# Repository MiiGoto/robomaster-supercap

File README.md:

# Firmware implementation — 2026-10-08

Current: Rev A STM32G474RET6 firmware source implemented; default SAFE_MONITOR_ONLY. Host logic tests and ARM builds are recorded in [docs/firmware_validation.md](docs/firmware_validation.md). No flash, option-byte write, real PWM/contact actuation or energizing was performed. Hardware/CAD is unchanged. Calibration, control gains, timing, BQ physical behavior and power limits require bench measurement and human review before first flash/energizing.

Current guides: [firmware architecture](docs/firmware_architecture.md), [operation](docs/supercap_user_guide.md), [commissioning](docs/firmware_commissioning.md), [CAN protocol](docs/can_protocol.md), [tuning](docs/control_tuning.md), [flash setup](docs/firmware_flash_setup.md).

## Historical records (preserved)

# PCB routing complete — 2026-10-07

**Current: Prototype Rev A CAD routing complete.** KiCad10.0.6の正式PCBでnative未接続0、全DRC0 errors/0 warnings、schematic parity0、ERC0 errors/0 warningsを確認した。全331ネット／1524 net-assigned pad recordsの物理接続と、設計manifestの1478 pad/net assignmentsを照合済み。これはCAD接続・規則検証であり、製造リリース、通電許可、120 W性能、競技適合の承認ではない。

一般銅箔間隔0.20 mm、承認済み39 ICの同一部品内Pad/Pad0.15 mmを維持した。新たなDRC除外・No ERC・規則緩和はない。未コミットの`.kicad_pro`設定展開は保持し、functional commitに含めない。詳細は[配線完了記録](docs/pcb_routing_completion.md)を現在の情報源とする。以下は過去時点の記録として保存する。

## Historical records (preserved)

# Routing checkpoint — 2026-10-04

**Routing incomplete.** 保存したPCBは電力7ネットの全パッド接続と、局所GND/一部信号配線を追加したcheckpoint。native未接続 **610本**（239 nets）、寸法・間隔DRC **0 errors/0 warnings**、schematic parity0。元の935本から325本を解消したが、配線完成/製造/通電/性能保証は意味しない。

現在の結果と残りを[配線作業記録](docs/pcb_routing_completion.md)で確認する。以下は以前の経緯を含む。

# Clearance approval update — 2026-10-04

39対象ICの内部fine-pitchパッド間0.15 mmをユーザー承認に基づき許容し、その他の銅箔間隔は0.20 mm以上を維持した。DRCの寸法・間隔違反0/0、未接続935本。[検証記録](docs/pcb_rev_a_validation.md)を現状として優先する。以下は変更前の経緯を含む。

# PCB engineering authorized — 2026-10-04

ユーザーがsurge・OC遮断時間・fuse/接触器協調・熱・放電時間の実測前にPCB配置/配線へ進むことを明示承認した。[現行PCB記録](docs/pcb_rev_a.md)を優先する。未実測の項目はPrototype Assumptionとして保持し、製造/通電/性能保証にはしない。以下の「PCB未承認/開始しない」は過去時点の記録として残す。

## Historical records (preserved)

# Prototype Rev A — 2026-10-04 delegated decisions

ユーザーの委任に基づき、セル監視RAM設定・exact passive選定・外部ベンチ遮断アセンブリ・保護/熱/放電検証基準を[現行選定書](docs/rev_a_design_freeze.md)へ確定した。選定はPrototype Assumption、実測検証は未実施。平均cap電流の初期上限9.5 A、OC約12 A、目標遮断0.5 µs、各link bulk6×470 µF、precharge timeout3 s。12 A/120 Wは後続の検証目標として保持。PCB placement/通電は開始しない。以下の2026-10-03以前の未選定表示は経緯記録であり、この選定書が優先する。

# Prototype Rev A — current status

2026-10-03 JST。**Current: Prototype Rev A schematic only.** Task2 architectureはユーザー採用承認済み。実機条件未確認は[Prototype envelope](docs/prototype_rev_a_envelope.md)に明示した **ASSUMPTION — MUST VERIFY ON PROTOTYPE** として隔離し、詳細electrical schematicを作成した。部品/保護閾値はprototype候補で性能保証ではない。[現行review](docs/rev_a_schematic_review.md)と[pinout](docs/pinout.md)が現在の設計記録。PCB placement/routing、firmware、通電、120W使用許可、競技適合、Task4開始は未承認。以下の旧status/approval pending/skeleton-only記述はhistorical recordであり現在statusではない。

[Validation record](docs/rev_a_validation.md): ERC0/0 baseline; current counts in validation record. External assembly and cell-monitor RAM profile are selected; hardware programming/qualification remain unperformed.

## Historical records (preserved)

# Task 4 current status — placement gate未通過

2026-10-03 JST。Task 3 base428ad10を保持。重大TBDと詳細回路未実装のため添付Task 4 §1に従いplacement/outline/footprint/routingは行わない。[独立review](docs/task4_review.md)が現在status、[PCB方針](docs/task4_pcb_strategy.md)は提案、[検査結果](docs/task4_baseline.md)は既存skeleton限定。Task 5へ進まない。以下は過去Task記録。

---

# Task 3 current status

2026-10-03 JST。Task 2案はユーザー採用承認済み。実bus/surge・peak継続/間隔・ambient/coolingは未確定（ユーザー回答：不明）。承認範囲と詳細回路gateは[Task 3 review gate](docs/task3_review_gate.md)を優先する。Task 3は候補評価まで進行中、詳細回路未実装。以下のTask 2承認待ち表示は承認範囲についてhistorical record。

---

# robomaster-supercap — Task 2

2026 RMUL用energy bufferの設計検討。英雄・歩兵・哨兵の競技assistが対象、EngineerはS5搭載許可対象外。Task1成果を保ち、Task2 architecture proposal・simulation・9-page KiCad conceptを追加。完成/検証済み回路ではない。

- [Requirements/status](requirements.md)
- [Architecture and 11 modes](docs/architecture.md)
- [Evidence and selected proposals](docs/task2_decisions.md)
- [Calculation results](simulation/results.md)
- [Safety](docs/safety.md) / [FMEA](docs/fmea.md)

第一案は9S 50F、4-switch bidirectional buck-boost、G474RE/LQFP64、signed high-side shunts、independent fault latch。全選定案はAssumptionとしてhuman review待ち、robot実bus/power/thermalはTBD。stored energyはOFF後も残る。
Roadmap: Task1完了→Task2 reviewable proposal→人間承認→別途Task3 component selection。mainへ自動mergeしない。詳細回路・routing・firmware・hardware testingなし。第三者PDF等は公開対象外、引用linkと出典のみ。

---

## Task 1 record (historical; Task 2 above takes precedence)

# robomaster-supercap

RoboMaster向けスーパーキャパシタ電源システムの要求・安全設計と開発基盤。
robot busの余剰energyを蓄え、必要時にassistし、状態監視とCAN通信を行う。

## Architecture

Robot Power Bus ⇄ Input Protection ⇄ Bidirectional Power Converter ⇄ Supercapacitor Bank。
MCUはbus/bank voltage、current、temperature、faultを監視する。独立保護がgate enableを拒否できる構成を要求する。
競技用の公式管理モジュール・検査経路を含む実接続は適用規則確認後に決める。

## Repository structure

```text
README.md / AGENTS.md / PROJECT_CONTEXT.md
requirements.md / references.md
hardware/kicad/        block-level project skeleton
firmware/controller/  future firmware requirements
simulation/           future model scope
docs/                 architecture, comparison, safety, FMEA, bringup
test/                 verification plan and publication audit
```

## Safety notice

蓄積energyは電源OFF後も残る。短絡・cell過電圧・逆流・熱暴走・connector arcを設計要件として扱う。
このrepositoryは通電可能な完成回路、製造データ、検証済みシステムを提供しない。
KiCad ERCが通っても、部品・netがないskeletonの安全性や動作は証明しない。

## Current status

Task 1文書とKiCad skeleton。詳細power stage、PCB layout、firmware、prototypeは未着手。
Confirmed / Assumption / TBDはPROJECT_CONTEXTとrequirementsに明示。
環境確認は [environment](docs/environment.md)、調査は [comparison](docs/reference_comparison.md)。

## Reference policy

外部設計は設計意図を比較し、[references.md](references.md)へ記録する。
外部回路図・PCB・PDF・画像・コードは取り込まない。ライセンスの衝突・不明点も記録する。
本プロジェクトの公開ライセンス選択はTBD。PUBLICであることだけで再利用許諾とはしない。

## Roadmap

1. Task 1: environment / repository / research / requirements / safety / KiCad skeleton。
2. 人間レビュー: 競技適用、robot仕様、capacitor候補、限界値、topology。
3. 承認後の別Task: 詳細回路、独立保護の検証、制御設計。
4. その後: PCB / firmware / 段階的bringup / fault injection / robot統合。

Task 2は自動開始しない。

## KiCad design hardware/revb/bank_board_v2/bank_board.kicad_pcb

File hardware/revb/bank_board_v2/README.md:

# Rev B バンク基板 v2（10S 2.7V 50F）

状態: 基板化済み・未試作（2026-10-11）。**動作・安全は未検証。通電前に人間レビューが必要。**
旧版 `hardware/revb/bank_board/` は参照用にそのまま残しています（下の「v1からの変更」参照）。

| 項目 | 値 |
|---|---|
| 外形 | 108.5 × 39.0 mm、2層 1.6 mm、銅 1 oz |
| セル | 50F 2.7V φ18×40 mm、リードピッチ 7.5 mm × 10本を立てて 5×2 配置（高さ約42 mm） |
| 直列経路 | 上段 C1→C5（左→右）、右端で折り返し、下段 C6→C10（右→左）。各ノードは表裏ベタ（幅約18 mm） |
| 外部接続 | XT30（J1、左端、縦型）1本のみ。pad1 = −（BANK_N）、pad2 = +（ヒューズ経由で BANK_P） |
| ヒューズ | 20 A ミニ平型（Littelfuse 0297020.WXNV、32 V / 1 kA 遮断）を直付け |
| クランプ | セル毎 TLV431 + PNP（BCP69-16）。部品は全て裏面（JLC SMT、片面60点） |
| 取付穴 | M3 × 2（セル4本の中間、上下段の間） |

## クランプ電圧（算術）
Vc = Vref × (1 + 22.9k/20k) + Iref × 22.9k

| | 値 |
|---|---|
| 標準 | 2.66 V |
| 25℃ 最小〜最大 | 2.644〜2.687 V（Vref 1.234〜1.246 V、抵抗0.1%、Iref 最大0.5 µA） |
| 温度 | TLV431BQ の Vref 変動（全温度範囲で最大31 mV）分、さらに ±0.02 V 程度 |

充電 26.2 V（平均 2.62 V/セル）はクランプ最小値より低いので、バランスが取れていれば満充電でもクランプは作動しません。

## v1（`hardware/revb/bank_board/`）からの変更
1. **TLV431 のピン配置を修正**: TI SLVS139Z Table 4-1 では SOT-23(DBZ) は 1 = REF、2 = CATHODE、3 = ANODE。v1 の注記（1 = A、2 = REF、3 = K）のままだとクランプが動作しない。
2. **XT30 の極性を修正**: KiCad の AMASS フットプリントは pad1 = −。v1 は pin1 = + だった。
3. クランプ電圧を 2.61 → 2.66 V に変更（22.1k → 22.9k）。
4. PNP のベースに 100 Ω を追加し、TLV431 のカソード電流を約7 mA 以下に制限（絶対最大 20 mA）。
5. ヒューズ・セル・XT30 のフットプリントと JLC 部品番号を確定。
6. テストポイントは削除（セルのリード穴がそのまま測定点になる）。

## 製造
- `fab/bank_board_gerber.zip`、`fab/jlcpcb_bom.csv`、`fab/jlcpcb_cpl.csv`（**実装面 = Bottom**）。
- CPL の回転は制御基板と同じ補正表（JLCKicadTools）＋裏面の換算（kicad-jlcpcb-tools と同じ式）。JLC のプレビューで、Q（SOT-223）のタブ、U（SOT-23）の1番ピン、Q のエミッタ/ベースの向きを確認してください。
- 手はんだ部品（LCSC で一緒に購入可）: J1 XT30UPB-M（C428721）、F1 0297020.WXNV（C151096）、セル10本（JLC/LCSC 在庫なし、別途手配）。
- セルの極性: シルクの斜線の半円が −、「+」印側が +。上段は右が +、下段は左が +。

## 未解決・要確認
1. **バイパス電流には上限がある**: 1セル当たり約0.6〜1.5 A（BCP69-16 の hFE 100〜250 × ベース電流約6 mA）、0.5 A で約1.3 W。容量のばらつきで一部のセルが先にクランプ電圧に達したとき、充電電流がこれを超えるとそのセルは 2.66 V を超えて上がり続ける。**満充電付近（例: バンク 25.5 V 以上）では、制御基板側で充電電流を 0.5 A 以下に絞る必要がある**（ファーム／設定で対応、未実装）。
2. PNP の発熱: 連続 1 W 以上は不可。タブを裏面のベタにつなぎ、ビアで表面のベタへ逃がしている。温度は実測が必要。
3. TLV431 + PNP のループ安定性は未検証（試作で発振を確認する。必要なら REF–K 間に補償容量を追加）。
4. セルのリード径: 穴径 1.2 mm で作っています。実物のリード径（一般に 0.8〜1.0 mm）を確認してください。
5. 取付穴: M3 ネジ頭はセル4本の間（空き直径約8.8 mm）に入る。ドライバーが届くか、実機の固定方法と合わせて確認。
6. XT30 はオス（制御基板 J102 と同じ）。ケーブルはメス–メス。電荷が残ったバンク側のピンが露出する点に注意。
7. KiCad 9 での DRC は未実施（KiCad 7 DRC: エラー0、未接続0。残りはライブラリ照合の警告のみ）。

## 再生成
```
cd tools/gen_sch && python3 s_bank.py <out>/bank_board.kicad_sch
kicad-cli sch export netlist --format kicadsexpr -o bank.net <out>/bank_board.kicad_sch
python3 tools/gen_pcb/build_bank.py bank.net <KiCad footprints dir> bank_board.kicad_pcb
python3 tools/gen_pcb/cpl_jlc.py bank_board.kicad_pcb tools/gen_pcb/cpl_rotations_db.csv jlcpcb_cpl.csv H1,H2,J1,F1,C1,C2,C3,C4,C5,C6,C7,C8,C9,C10
```

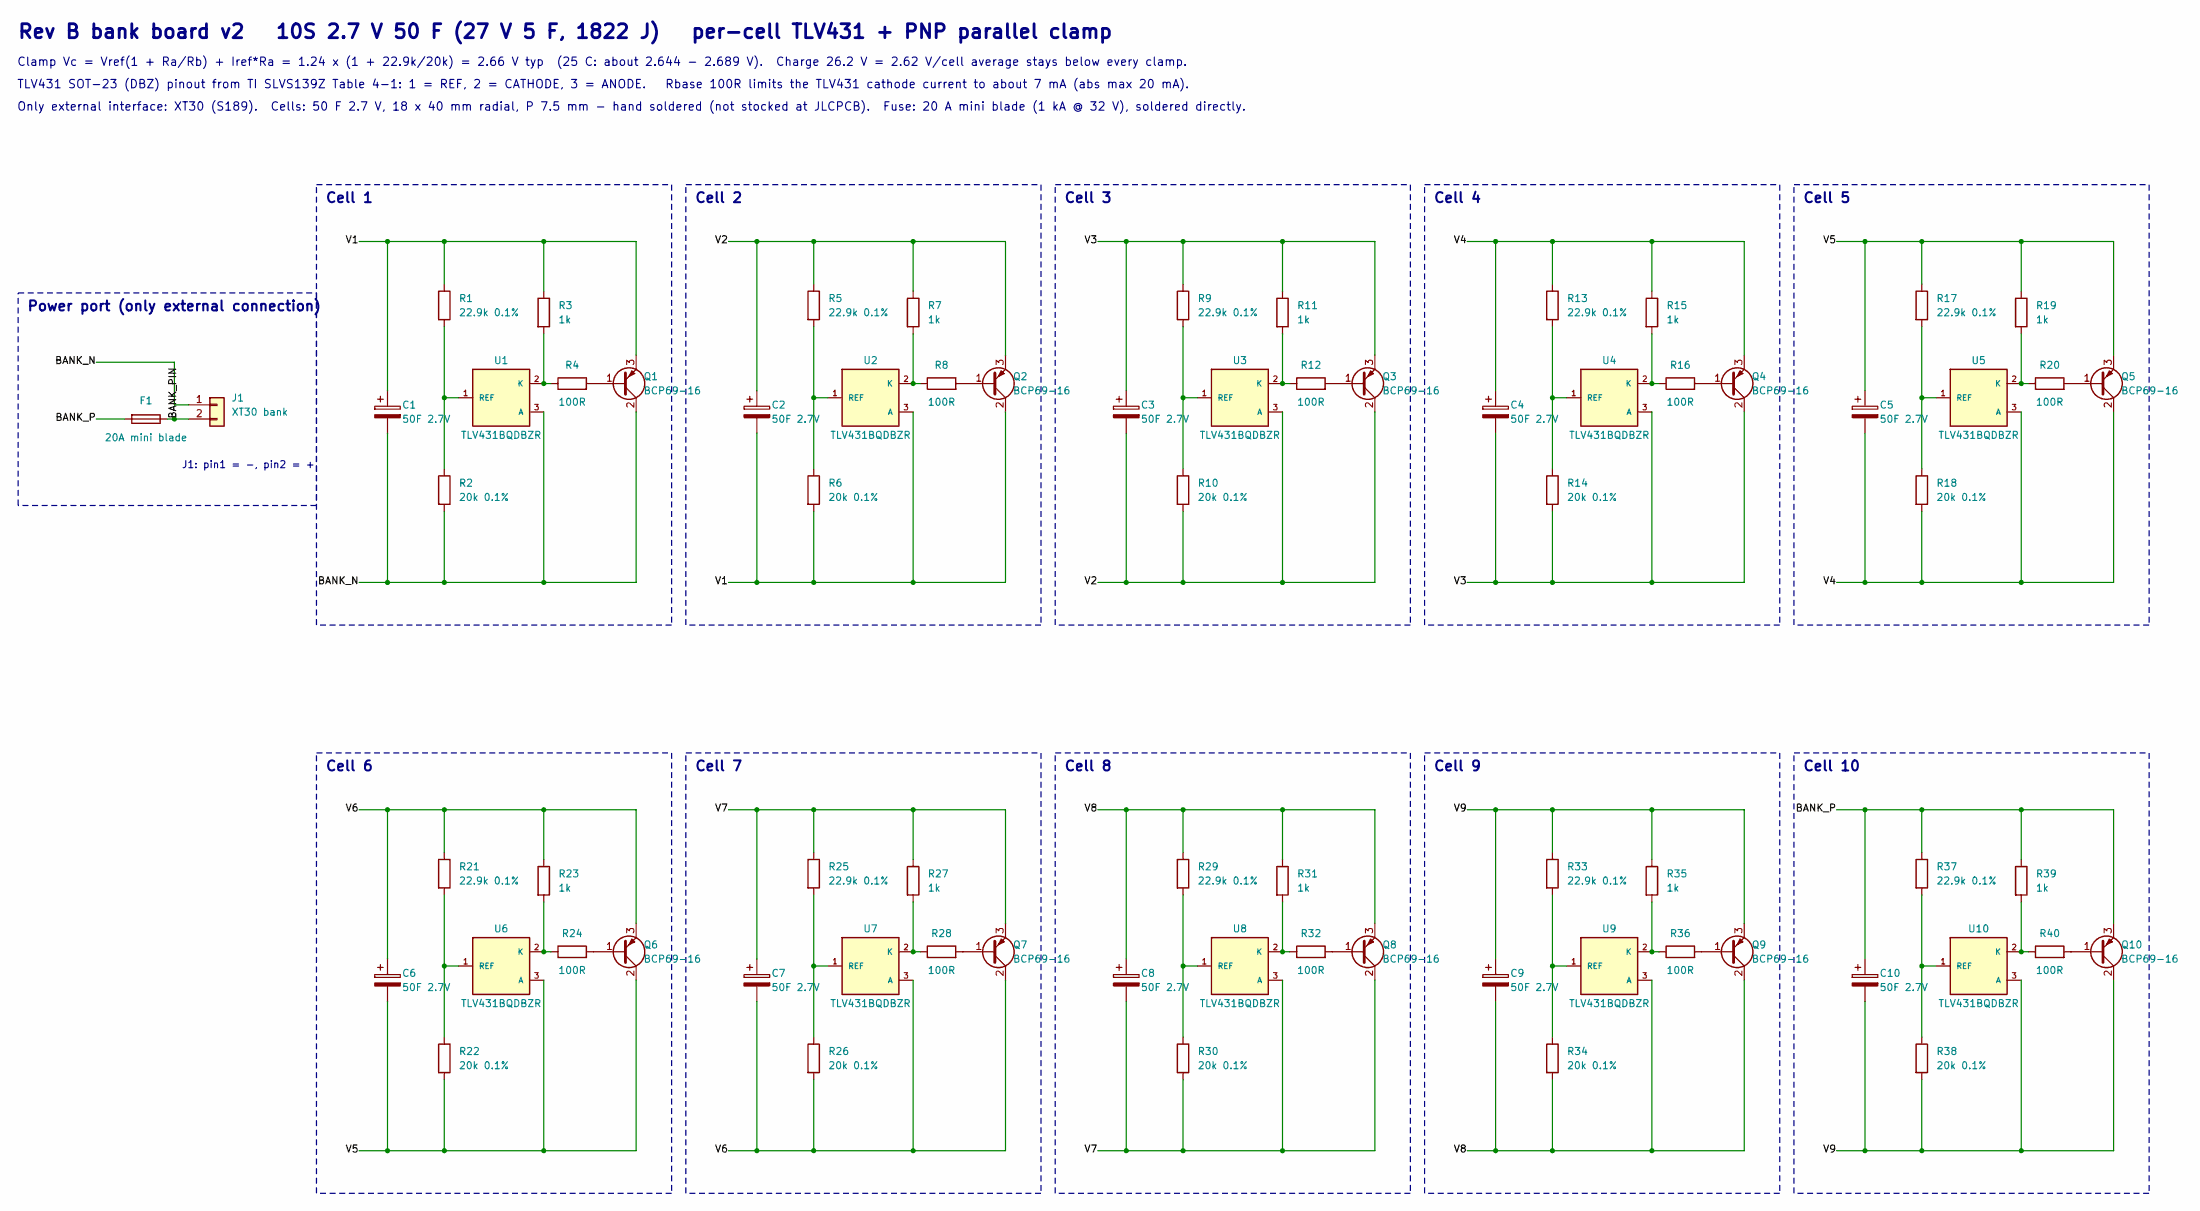
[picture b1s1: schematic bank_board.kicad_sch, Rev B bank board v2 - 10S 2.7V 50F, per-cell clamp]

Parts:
C1, C2, C3, C4, C5, C6, C7, C8, C9, C10: 50F 2.7V; CP_Radial_D18.0mm_P7.50mm
F1: 20A mini blade; Fuse_Blade_Mini_directSolder; LCSC C151096
J1: XT30 bank; AMASS_XT30UPB-M_1x02_P5.0mm_Vertical; LCSC C428721
Q1, Q2, Q3, Q4, Q5, Q6, Q7, Q8, Q9, Q10: BCP69-16; SOT-223-3_TabPin2; LCSC C75011
R1, R5, R9, R13, R17, R21, R25, R29, R33, R37: 22.9k 0.1%; R_0603_1608Metric; LCSC C4197857
R2, R6, R10, R14, R18, R22, R26, R30, R34, R38: 20k 0.1%; R_0603_1608Metric; LCSC C723637
R3, R7, R11, R15, R19, R23, R27, R31, R35, R39: 1k; R_0603_1608Metric; LCSC C21190
R4, R8, R12, R16, R20, R24, R28, R32, R36, R40: 100R; R_0603_1608Metric; LCSC C22775
U1, U2, U3, U4, U5, U6, U7, U8, U9, U10: TLV431BQDBZR; SOT-23; LCSC C398374

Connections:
/BANK_N: C1.2, J1.1, Q1.2 (C), R2.2, U1.3 (A)
/BANK_P: C10.1, F1.2, Q10.3 (E), R37.1, R39.1
/BANK_PIN: F1.1, J1.2
/V1: C1.1, C2.2, Q1.3 (E), Q2.2 (C), R1.1, R3.1, R6.2, U2.3 (A)
/V2: C2.1, C3.2, Q2.3 (E), Q3.2 (C), R5.1, R7.1, R10.2, U3.3 (A)
/V3: C3.1, C4.2, Q3.3 (E), Q4.2 (C), R9.1, R11.1, R14.2, U4.3 (A)
/V4: C4.1, C5.2, Q4.3 (E), Q5.2 (C), R13.1, R15.1, R18.2, U5.3 (A)
/V5: C5.1, C6.2, Q5.3 (E), Q6.2 (C), R17.1, R19.1, R22.2, U6.3 (A)
/V6: C6.1, C7.2, Q6.3 (E), Q7.2 (C), R21.1, R23.1, R26.2, U7.3 (A)
/V7: C7.1, C8.2, Q7.3 (E), Q8.2 (C), R25.1, R27.1, R30.2, U8.3 (A)
/V8: C8.1, C9.2, Q8.3 (E), Q9.2 (C), R29.1, R31.1, R34.2, U9.3 (A)
/V9: C9.1, C10.2, Q9.3 (E), Q10.2 (C), R33.1, R35.1, R38.2, U10.3 (A)
unnamed: Q1.1 (B), R4.2
unnamed: Q2.1 (B), R8.2
unnamed: Q3.1 (B), R12.2
unnamed: Q4.1 (B), R16.2
unnamed: Q5.1 (B), R20.2
unnamed: Q6.1 (B), R24.2
unnamed: Q7.1 (B), R28.2
unnamed: Q8.1 (B), R32.2
unnamed: Q9.1 (B), R36.2
unnamed: Q10.1 (B), R40.2
unnamed: R3.2, R4.1, U1.2 (K)
unnamed: R1.2, R2.1, U1.1 (REF)
unnamed: R7.2, R8.1, U2.2 (K)
unnamed: R5.2, R6.1, U2.1 (REF)
unnamed: R11.2, R12.1, U3.2 (K)
unnamed: R9.2, R10.1, U3.1 (REF)
unnamed: R15.2, R16.1, U4.2 (K)
unnamed: R13.2, R14.1, U4.1 (REF)
unnamed: R19.2, R20.1, U5.2 (K)
unnamed: R17.2, R18.1, U5.1 (REF)
unnamed: R23.2, R24.1, U6.2 (K)
unnamed: R21.2, R22.1, U6.1 (REF)
unnamed: R27.2, R28.1, U7.2 (K)
unnamed: R25.2, R26.1, U7.1 (REF)
unnamed: R31.2, R32.1, U8.2 (K)
unnamed: R29.2, R30.1, U8.1 (REF)
unnamed: R35.2, R36.1, U9.2 (K)
unnamed: R33.2, R34.1, U9.1 (REF)
unnamed: R39.2, R40.1, U10.2 (K)
unnamed: R37.2, R38.1, U10.1 (REF)

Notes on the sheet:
Rev B bank board v2 10S 2.7 V 50 F (27 V 5 F, 1822 J) per-cell TLV431 + PNP parallel clamp
Clamp Vc = Vref(1 + Ra/Rb) + Iref*Ra = 1.24 x (1 + 22.9k/20k) = 2.66 V typ (25 C: about 2.644 - 2.689 V). Charge 26.2 V = 2.62 V/cell average stays below every clamp.
TLV431 SOT-23 (DBZ) pinout from TI SLVS139Z Table 4-1: 1 = REF, 2 = CATHODE, 3 = ANODE. Rbase 100R limits the TLV431 cathode current to about 7 mA (abs max 20 mA).
Only external interface: XT30 (S189). Cells: 50 F 2.7 V, 18 x 40 mm radial, P 7.5 mm - hand soldered (not stocked at JLCPCB). Fuse: 20 A mini blade (1 kA @ 32 V), soldered directly.
Power port (only external connection)
J1: pin1 = -, pin2 = +
Cell 1
Cell 2
Cell 3
Cell 4
Cell 5
Cell 6
Cell 7
Cell 8
Cell 9
Cell 10

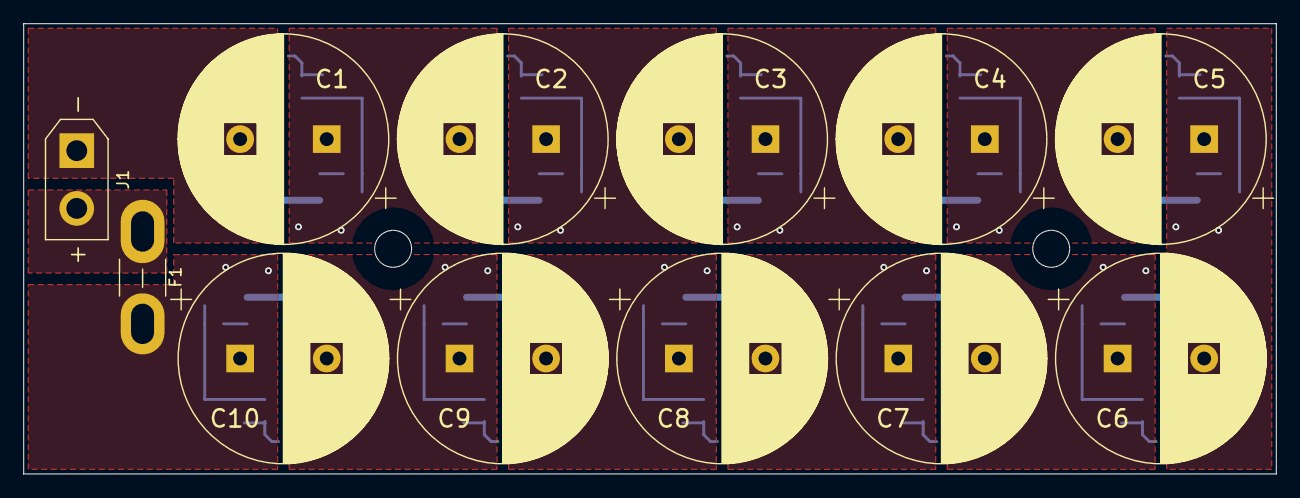
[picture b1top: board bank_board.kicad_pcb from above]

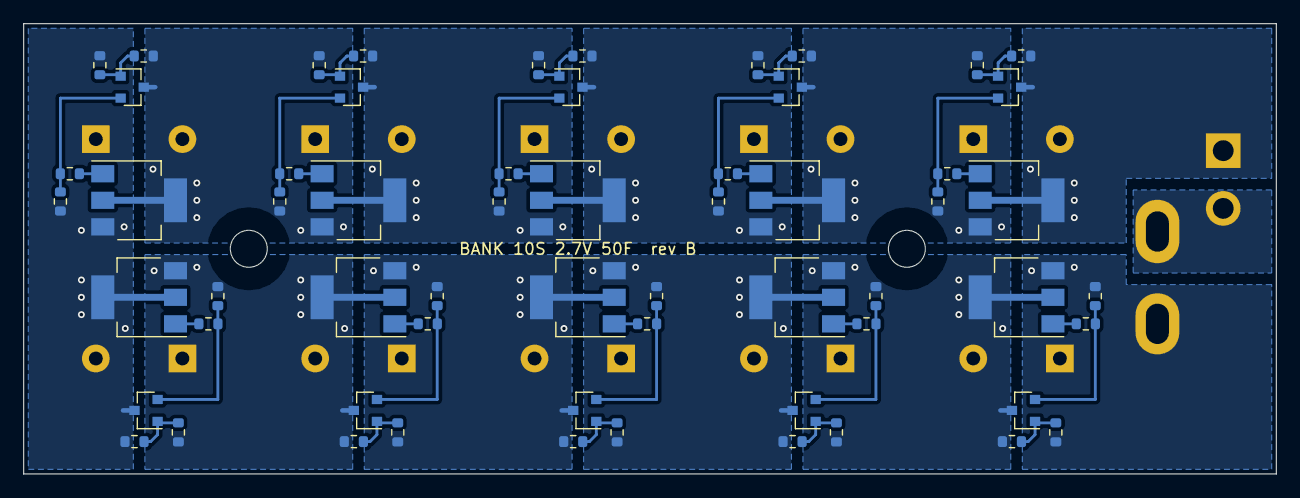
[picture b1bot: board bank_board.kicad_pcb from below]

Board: 2 copper layers, 108.5 x 39.0 mm, 74 parts (60 on the bottom side), 42 nets.

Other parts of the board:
H1, H2: M3; MountingHole_3.2mm_M3

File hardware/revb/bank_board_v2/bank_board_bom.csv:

Ref,Value,LCSC,Footprint,Symbol
"J1","XT30 bank","C428721","Connector_AMASS:AMASS_XT30UPB-M_1x02_P5.0mm_Vertical","rev:CON2"
"F1","20A mini blade","C151096","Fuse:Fuse_Blade_Mini_directSolder","rev:FUSE"
"C1","50F 2.7V","","Capacitor_THT:CP_Radial_D18.0mm_P7.50mm","rev:CP"
"R1","22.9k 0.1%","C4197857","Resistor_SMD:R_0603_1608Metric","rev:R"
"R2","20k 0.1%","C723637","Resistor_SMD:R_0603_1608Metric","rev:R"
"U1","TLV431BQDBZR","C398374","Package_TO_SOT_SMD:SOT-23","rev:TLV431_DBZ"
"R3","1k","C21190","Resistor_SMD:R_0603_1608Metric","rev:R"
"R4","100R","C22775","Resistor_SMD:R_0603_1608Metric","rev:R"
"Q1","BCP69-16","C75011","Package_TO_SOT_SMD:SOT-223-3_TabPin2","rev:PNP"
"C2","50F 2.7V","","Capacitor_THT:CP_Radial_D18.0mm_P7.50mm","rev:CP"
"R5","22.9k 0.1%","C4197857","Resistor_SMD:R_0603_1608Metric","rev:R"
"R6","20k 0.1%","C723637","Resistor_SMD:R_0603_1608Metric","rev:R"
"U2","TLV431BQDBZR","C398374","Package_TO_SOT_SMD:SOT-23","rev:TLV431_DBZ"
"R7","1k","C21190","Resistor_SMD:R_0603_1608Metric","rev:R"
"R8","100R","C22775","Resistor_SMD:R_0603_1608Metric","rev:R"
"Q2","BCP69-16","C75011","Package_TO_SOT_SMD:SOT-223-3_TabPin2","rev:PNP"
"C3","50F 2.7V","","Capacitor_THT:CP_Radial_D18.0mm_P7.50mm","rev:CP"
"R9","22.9k 0.1%","C4197857","Resistor_SMD:R_0603_1608Metric","rev:R"
"R10","20k 0.1%","C723637","Resistor_SMD:R_0603_1608Metric","rev:R"
"U3","TLV431BQDBZR","C398374","Package_TO_SOT_SMD:SOT-23","rev:TLV431_DBZ"
"R11","1k","C21190","Resistor_SMD:R_0603_1608Metric","rev:R"
"R12","100R","C22775","Resistor_SMD:R_0603_1608Metric","rev:R"
"Q3","BCP69-16","C75011","Package_TO_SOT_SMD:SOT-223-3_TabPin2","rev:PNP"
"C4","50F 2.7V","","Capacitor_THT:CP_Radial_D18.0mm_P7.50mm","rev:CP"
"R13","22.9k 0.1%","C4197857","Resistor_SMD:R_0603_1608Metric","rev:R"
"R14","20k 0.1%","C723637","Resistor_SMD:R_0603_1608Metric","rev:R"
"U4","TLV431BQDBZR","C398374","Package_TO_SOT_SMD:SOT-23","rev:TLV431_DBZ"
"R15","1k","C21190","Resistor_SMD:R_0603_1608Metric","rev:R"
"R16","100R","C22775","Resistor_SMD:R_0603_1608Metric","rev:R"
"Q4","BCP69-16","C75011","Package_TO_SOT_SMD:SOT-223-3_TabPin2","rev:PNP"
"C5","50F 2.7V","","Capacitor_THT:CP_Radial_D18.0mm_P7.50mm","rev:CP"
"R17","22.9k 0.1%","C4197857","Resistor_SMD:R_0603_1608Metric","rev:R"
"R18","20k 0.1%","C723637","Resistor_SMD:R_0603_1608Metric","rev:R"
"U5","TLV431BQDBZR","C398374","Package_TO_SOT_SMD:SOT-23","rev:TLV431_DBZ"
"R19","1k","C21190","Resistor_SMD:R_0603_1608Metric","rev:R"
"R20","100R","C22775","Resistor_SMD:R_0603_1608Metric","rev:R"
"Q5","BCP69-16","C75011","Package_TO_SOT_SMD:SOT-223-3_TabPin2","rev:PNP"
"C6","50F 2.7V","","Capacitor_THT:CP_Radial_D18.0mm_P7.50mm","rev:CP"
"R21","22.9k 0.1%","C4197857","Resistor_SMD:R_0603_1608Metric","rev:R"
"R22","20k 0.1%","C723637","Resistor_SMD:R_0603_1608Metric","rev:R"
"U6","TLV431BQDBZR","C398374","Package_TO_SOT_SMD:SOT-23","rev:TLV431_DBZ"
"R23","1k","C21190","Resistor_SMD:R_0603_1608Metric","rev:R"
"R24","100R","C22775","Resistor_SMD:R_0603_1608Metric","rev:R"
"Q6","BCP69-16","C75011","Package_TO_SOT_SMD:SOT-223-3_TabPin2","rev:PNP"
"C7","50F 2.7V","","Capacitor_THT:CP_Radial_D18.0mm_P7.50mm","rev:CP"
"R25","22.9k 0.1%","C4197857","Resistor_SMD:R_0603_1608Metric","rev:R"
"R26","20k 0.1%","C723637","Resistor_SMD:R_0603_1608Metric","rev:R"
"U7","TLV431BQDBZR","C398374","Package_TO_SOT_SMD:SOT-23","rev:TLV431_DBZ"
"R27","1k","C21190","Resistor_SMD:R_0603_1608Metric","rev:R"
"R28","100R","C22775","Resistor_SMD:R_0603_1608Metric","rev:R"
"Q7","BCP69-16","C75011","Package_TO_SOT_SMD:SOT-223-3_TabPin2","rev:PNP"
"C8","50F 2.7V","","Capacitor_THT:CP_Radial_D18.0mm_P7.50mm","rev:CP"
"R29","22.9k 0.1%","C4197857","Resistor_SMD:R_0603_1608Metric","rev:R"
"R30","20k 0.1%","C723637","Resistor_SMD:R_0603_1608Metric","rev:R"
"U8","TLV431BQDBZR","C398374","Package_TO_SOT_SMD:SOT-23","rev:TLV431_DBZ"
"R31","1k","C21190","Resistor_SMD:R_0603_1608Metric","rev:R"
"R32","100R","C22775","Resistor_SMD:R_0603_1608Metric","rev:R"
"Q8","BCP69-16","C75011","Package_TO_SOT_SMD:SOT-223-3_TabPin2","rev:PNP"
"C9","50F 2.7V","","Capacitor_THT:CP_Radial_D18.0mm_P7.50mm","rev:CP"
"R33","22.9k 0.1%","C4197857","Resistor_SMD:R_0603_1608Metric","rev:R"
"R34","20k 0.1%","C723637","Resistor_SMD:R_0603_1608Metric","rev:R"
"U9","TLV431BQDBZR","C398374","Package_TO_SOT_SMD:SOT-23","rev:TLV431_DBZ"
"R35","1k","C21190","Resistor_SMD:R_0603_1608Metric","rev:R"
"R36","100R","C22775","Resistor_SMD:R_0603_1608Metric","rev:R"
"Q9","BCP69-16","C75011","Package_TO_SOT_SMD:SOT-223-3_TabPin2","rev:PNP"
"C10","50F 2.7V","","Capacitor_THT:CP_Radial_D18.0mm_P7.50mm","rev:CP"
"R37","22.9k 0.1%","C4197857","Resistor_SMD:R_0603_1608Metric","rev:R"
"R38","20k 0.1%","C723637","Resistor_SMD:R_0603_1608Metric","rev:R"
"U10","TLV431BQDBZR","C398374","Package_TO_SOT_SMD:SOT-23","rev:TLV431_DBZ"
"R39","1k","C21190","Resistor_SMD:R_0603_1608Metric","rev:R"
"R40","100R","C22775","Resistor_SMD:R_0603_1608Metric","rev:R"
"Q10","BCP69-16","C75011","Package_TO_SOT_SMD:SOT-223-3_TabPin2","rev:PNP"

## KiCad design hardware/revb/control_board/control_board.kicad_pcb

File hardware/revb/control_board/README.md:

# Rev B 制御基板(案Y)

- `charger.kicad_sch`: ブロック1(入力保護、直列PMOS、LM5176電力段)。仮設計。機能ごとの枠(A〜H)で整理済み。charger.pdfは確認用の出力。
- 生成: `tools/gen_sch/charger.py`(`python3 charger.py <出力先>`)。シンボルは `rev.kicad_sym` に同梱。
- 接続はネットラベルのみ(配線なし)。レイアウトは未整理。
- ERC(KiCad 9.0、2026-10-10): エラー0、警告4(FET4個のフットプリント名がライブラリに無い。未確定)。
- 未確認: ISNS+/-の極性、MODE(ヒカップ)、BIAS=NODE、UVLO値、FET/インダクタのフットプリント。
- 次のブロック: MCU(STM32G431)、電圧/電流計測、保護(OV比較器、PMOS_EN、CHG_INH)、補助電源。

## 更新(2026-10-10)
- `control.kicad_sch`: ブロック2(補助電源、STM32G431、計測、保護/イネーブル論理、CAN/UART)。`control_board.kicad_sch` が階層ルート。ERC 0 errors(コミット45ba58d)。
- 上の「次のブロック」は実施済み。残り: フットプリント確定、部品在庫確認、バンク基板との整合。

## 改訂(2026-10-11): 配線ありの回路図に描き直し
- 4シート構成: `power_input`(入力保護・直列PMOS・入力シャント・ISNSオフセット・INA240)、`buckboost`(LM5176・電力段・出力ノード・キャパシタ側電流)、`mcu`(補助3.3V・STM32G431・CAN・UART・LED)、`protect_sense`(分圧・基準・OV比較器・イネーブル論理)。ルートは `control_board.kicad_sch`。PDF: `control_board.pdf`。
- 生成: `tools/gen_sch/build2.py <出力先>`(kisch2.py: ワイヤ・電源シンボル描画、生成後にKiCadのネットリストと意図ネットを照合)。
- ERC(KiCad 9.0、2026-10-11): エラー0、警告0。
- 旧版(ラベルのみ)は `_superseded/` に移動。
- レビューで直した点: 2N7002の記号ピン(GDS→GSD、SOT-23でD/S逆だった)、電力FETの記号(3ピン→TDSON-8の8ピン対応)、FET耐圧40V→60V級、出力コンデンサ35V→50V、NODEにTVS追加、比較器にヒステリシス追加、EN_PMOS直列1k→4.7k、補助電源入力に10R追加、CAN終端(DNP)追加、ISNSオフセット回路(MCUのDACで入力電流上限を可変)追加、ICAP_SをPA4→PA6へ移動(PA4はDAC)。
- 未決: 充電電圧26.2Vか25.6V(バンク基板のクランプ下限との関係、docs/revb/bank_board.md)、電力FET型番、インダクタ・ヒューズ・電解の型番とフットプリント、CAN/審判UARTコネクタのピン配置、MODE抵抗の意味(データシート再確認)。

## 改訂(2026-10-11): 部品確定・基板(配置/配線)
- 部品はJLCPCBで在庫・価格を確認して選定(Basic/Preferred優先)。一覧: `jlcpcb_bom.csv`(59行、LCSC番号付き)。主な部品: 電力FET NTMFS5C670NL(C179626)×4、インダクタ SLO1365S100MTT 10uH(C242228)、ヒューズ 10A 1206、TVS SMBJ30A、XT30UPB-M(縦型)×3、小信号は0402。
- 定数変更: 出力 1.5M/47k = 26.33 V(Basic値)、UVLO 220k/15k ≈ 19.3 V、入力OV 150k/6.8k ≈ 28.8 V、ノードOV 100k/4.7k ≈ 27.8 V、電流検出 10→12 mΩ(谷/ピーク制限 ≈6.7 A/10 A)。CANはGH 2ピン(1=CANH, 2=CANL)。終端120RとSWDヘッダは未実装(DNP)。
- XT30のピン: AMASSフットプリントに合わせ **pin1 = −(GND)、pin2 = +** に修正。
- 基板 `control_board.kicad_pcb`: 68×57 mm(Taobao基板 69×58 mm 以内)、4層(F: 部品+電力パワープレーン、In1: GND、In2: 信号、B: 信号+GND)、片面実装、M3穴×3。
- 配線: 電力経路は銅箔ゾーン、信号はFreerouting+補助ルータ(`tools/gen_pcb/`)。KiCad 9.0 DRC(2026-10-11): エラー0、未配線0。警告154は主にライブラリ版との差異(フットプリントは旧ライブラリ版を埋め込み)とシルク重なり。
- 製造データ: `fab/control_board_gerber.zip`、`fab/jlcpcb_cpl.csv`、`jlcpcb_bom.csv`。**発注前にJLCPCBのプレビューで回転・極性(XT30、ダイオード、電解、IC1番ピン)を必ず確認すること。**
- 未検証・要確認: SO-8FL(FET)とSLO1365(インダクタ)は近い既存フットプリントを流用、CSLOPE 220p(Rcs 12 mΩで再計算)、ゲート配線が長い箇所あり(昇圧側)、ビア0.5/0.25 mmが42個(JLCの追加料金対象の可能性)。

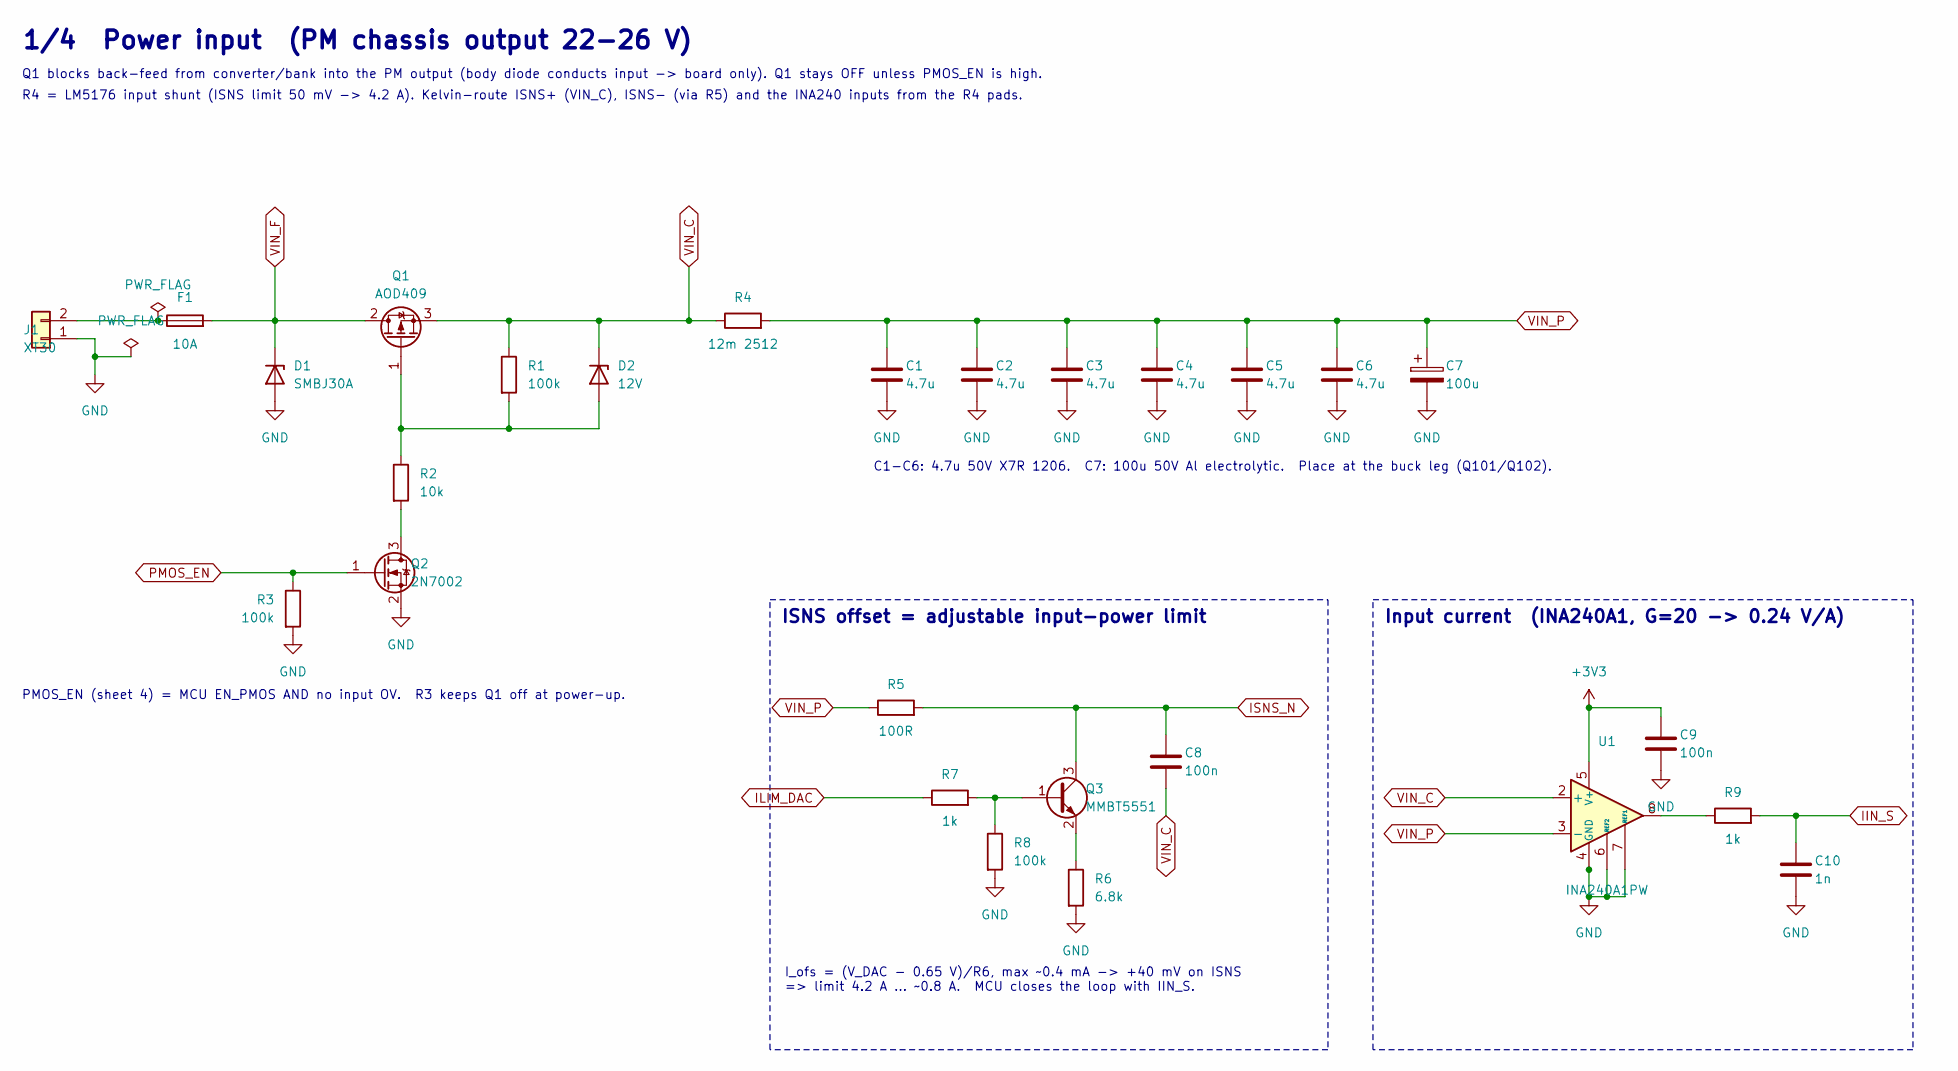
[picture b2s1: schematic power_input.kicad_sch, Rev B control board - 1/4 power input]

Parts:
C1, C2, C3, C4, C5, C6: 4.7u; C_1206_3216Metric; LCSC C29823
C7: 100u; CP_Elec_6.3x7.7; LCSC C3151829
C8, C9: 100n; C_0402_1005Metric; LCSC C1525
C10: 1n; C_0402_1005Metric; LCSC C1523
D1: SMBJ30A; D_SMB; LCSC C19077584
D2: 12V; D_SOD-123; LCSC C19077426
F1: 10A; Fuse_1206_3216Metric; LCSC C52988557
J1: XT30; AMASS_XT30UPB-M_1x02_P5.0mm_Vertical; LCSC C428721
Q1: AOD409; TO-252-2; LCSC C36220
Q2: 2N7002; SOT-23; LCSC C8545
Q3: MMBT5551; SOT-23; LCSC C2145
R1, R3, R8: 100k; R_0402_1005Metric; LCSC C25741
R2: 10k; R_0402_1005Metric; LCSC C25744
R4: 12m 2512; R_2512_6332Metric; LCSC C49164692
R5: 100R; R_0402_1005Metric; LCSC C25076
R6: 6.8k; R_0402_1005Metric; LCSC C25917
R7, R9: 1k; R_0402_1005Metric; LCSC C11702
U1: INA240A1PW; TSSOP-8_4.4x3mm_P0.65mm; LCSC C93965

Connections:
+3V3: C9.1, U1.5 (V+); also elsewhere on the board
GND: C1.2, C2.2, C3.2, C4.2, C5.2, C6.2, C7.2, C9.2, C10.2, D1.2 (A), J1.1, Q2.2 (S), R3.2, R6.2, R8.2, U1.1 (GND), U1.4 (GND), U1.6 (REF2), U1.7 (REF1); also elsewhere on the board
IIN_S: C10.1, R9.2; also elsewhere on the board
ILIM_DAC: R7.1; also elsewhere on the board
ISNS_N: C8.1, Q3.3 (C), R5.2; also elsewhere on the board
unnamed: D2.2 (A), Q1.1 (G), R1.2, R2.1
unnamed: F1.1, J1.2
unnamed: Q2.3 (D), R2.2
unnamed: Q3.1 (B), R7.2, R8.1
unnamed: Q3.2 (E), R6.1
unnamed: R9.1, U1.8
PMOS_EN: Q2.1 (G), R3.1; also elsewhere on the board
VIN_C: C8.2, D2.1 (K), Q1.3 (S), R1.1, R4.1, U1.2 (+); also elsewhere on the board
VIN_F: D1.1 (K), F1.2, Q1.2 (D); also elsewhere on the board
VIN_P: C1.1, C2.1, C3.1, C4.1, C5.1, C6.1, C7.1, R4.2, R5.1, U1.3 (-); also elsewhere on the board

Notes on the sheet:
1/4 Power input (PM chassis output 22-26 V)
Q1 blocks back-feed from converter/bank into the PM output (body diode conducts input -> board only). Q1 stays OFF unless PMOS_EN is high.
R4 = LM5176 input shunt (ISNS limit 50 mV -> 4.2 A). Kelvin-route ISNS+ (VIN_C), ISNS- (via R5) and the INA240 inputs from the R4 pads.
PMOS_EN (sheet 4) = MCU EN_PMOS AND no input OV. R3 keeps Q1 off at power-up.
C1-C6: 4.7u 50V X7R 1206. C7: 100u 50V Al electrolytic. Place at the buck leg (Q101/Q102).
ISNS offset = adjustable input-power limit
I_ofs = (V_DAC - 0.65 V)/R6, max ~0.4 mA -> +40 mV on ISNS => limit 4.2 A ... ~0.8 A. MCU closes the loop with IIN_S.
Input current (INA240A1, G=20 -> 0.24 V/A)

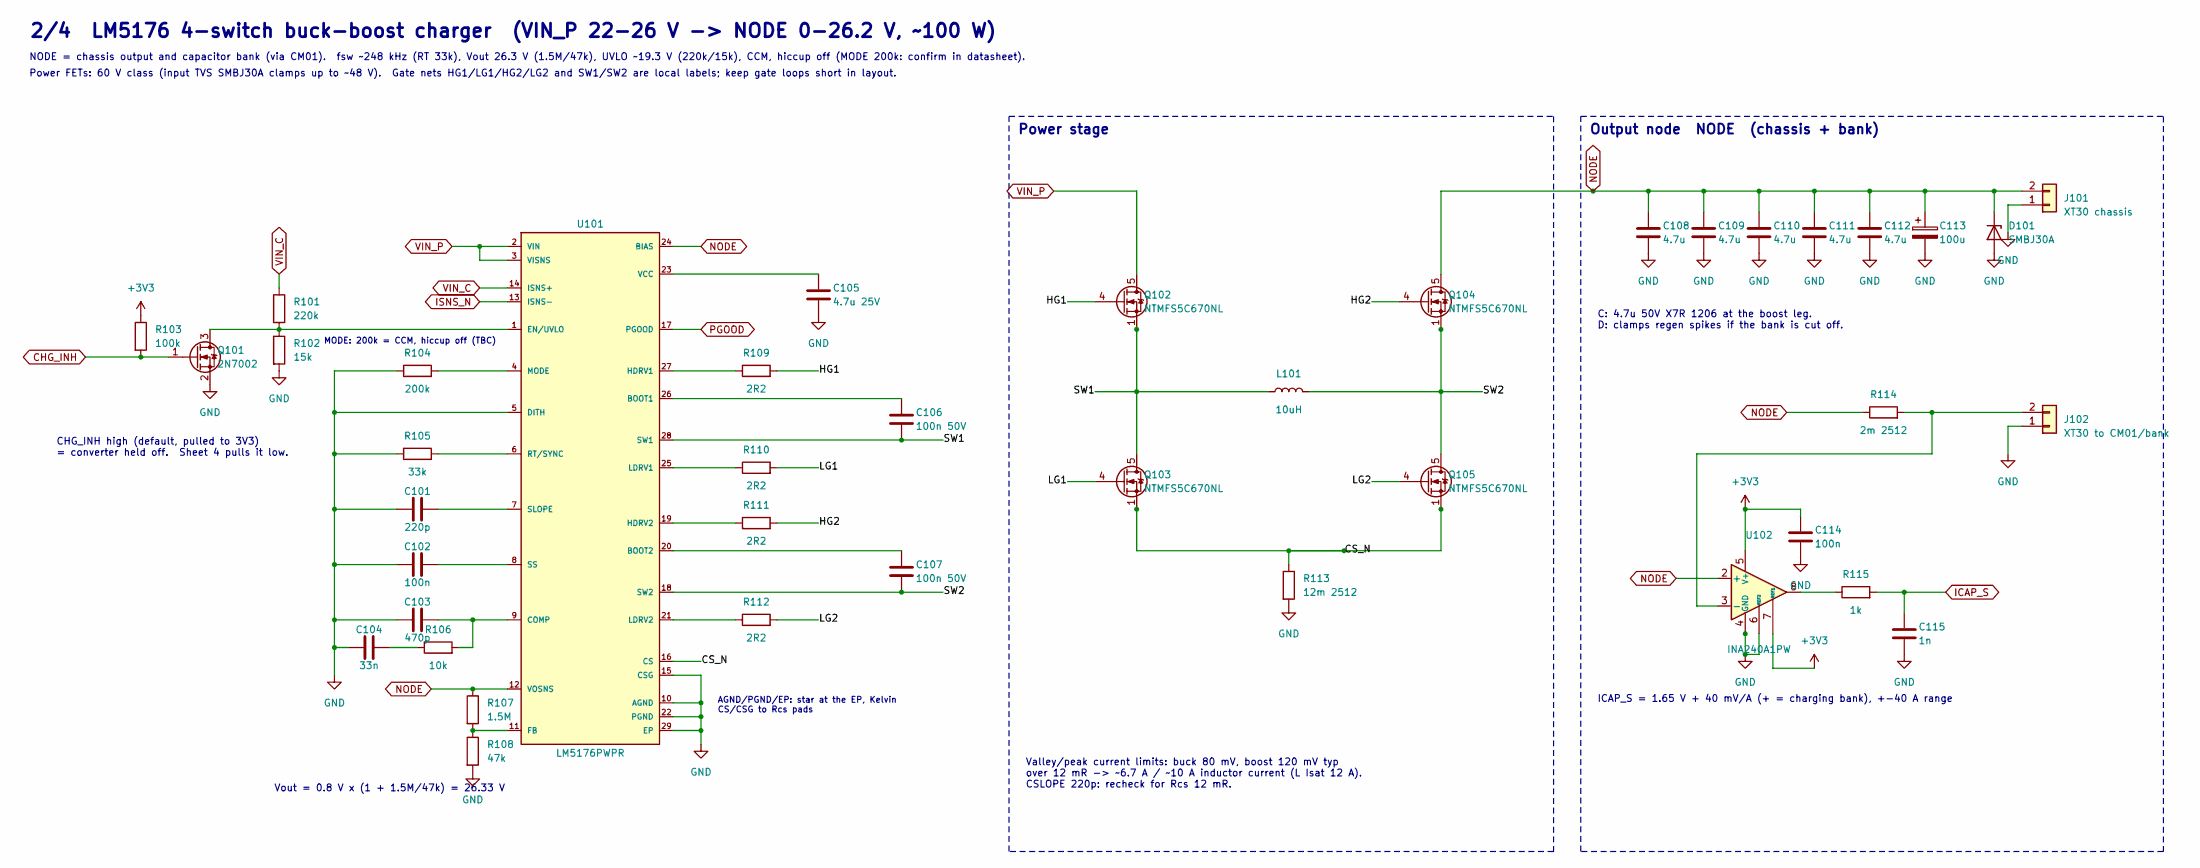
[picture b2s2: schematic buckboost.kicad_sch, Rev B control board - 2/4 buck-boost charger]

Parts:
C101: 220p; C_0402_1005Metric; LCSC C1530
C102, C114: 100n; C_0402_1005Metric; LCSC C1525
C103: 470p; C_0402_1005Metric; LCSC C1537
C104: 33n; C_0603_1608Metric; LCSC C21117
C105: 4.7u 25V; C_0805_2012Metric; LCSC C1779
C106, C107: 100n 50V; C_0603_1608Metric; LCSC C14663
C108, C109, C110, C111, C112: 4.7u; C_1206_3216Metric; LCSC C29823
C113: 100u; CP_Elec_6.3x7.7; LCSC C3151829
C115: 1n; C_0402_1005Metric; LCSC C1523
D101: SMBJ30A; D_SMB; LCSC C19077584
J101: XT30 chassis; AMASS_XT30UPB-M_1x02_P5.0mm_Vertical; LCSC C428721
J102: XT30 to CM01/bank; AMASS_XT30UPB-M_1x02_P5.0mm_Vertical; LCSC C428721
L101: 10uH; L_Wuerth_HCI-1365; LCSC C242228
Q101: 2N7002; SOT-23; LCSC C8545
Q102, Q103, Q104, Q105: NTMFS5C670NL; TDSON-8-1; LCSC C179626
R101: 220k; R_0402_1005Metric; LCSC C25767
R102: 15k; R_0402_1005Metric; LCSC C25756
R103: 100k; R_0402_1005Metric; LCSC C25741
R104: 200k; R_0402_1005Metric; LCSC C25764
R105: 33k; R_0402_1005Metric; LCSC C25779
R106: 10k; R_0402_1005Metric; LCSC C25744
R107: 1.5M; R_0603_1608Metric; LCSC C4172
R108: 47k; R_0402_1005Metric; LCSC C25792
R109, R110, R111, R112: 2R2; R_0603_1608Metric; LCSC C22939
R113: 12m 2512; R_2512_6332Metric; LCSC C49164692
R114: 2m 2512; R_2512_6332Metric; LCSC C7420017
R115: 1k; R_0402_1005Metric; LCSC C11702
U101: LM5176PWPR; HTSSOP-28-1EP_4.4x9.7mm_P0.65mm_EP2.85x5.4mm; LCSC C442493
U102: INA240A1PW; TSSOP-8_4.4x3mm_P0.65mm; LCSC C93965

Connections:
+3V3: C114.1, R103.1, U102.5 (V+), U102.7 (REF1); also elsewhere on the board
/buckboost/CS_N: Q103.1 (S), Q103.2 (S), Q103.3 (S), Q105.1 (S), Q105.2 (S), Q105.3 (S), R113.1, U101.16 (CS)
/buckboost/HG1: Q102.4 (G), R109.2
/buckboost/HG2: Q104.4 (G), R111.2
/buckboost/LG1: Q103.4 (G), R110.2
/buckboost/LG2: Q105.4 (G), R112.2
/buckboost/SW1: C106.2, L101.1, Q102.1 (S), Q102.2 (S), Q102.3 (S), Q103.5 (D), U101.28 (SW1)
/buckboost/SW2: C107.2, L101.2, Q104.1 (S), Q104.2 (S), Q104.3 (S), Q105.5 (D), U101.18 (SW2)
CHG_INH: Q101.1 (G), R103.2; also elsewhere on the board
GND: C101.1, C102.1, C103.1, C104.1, C105.2, C108.2, C109.2, C110.2, C111.2, C112.2, C113.2, C114.2, C115.2, D101.2 (A), J101.1, J102.1, Q101.2 (S), R102.2, R104.1, R105.1, R108.2, R113.2, U101.5 (DITH), U101.10 (AGND), U101.15 (CSG), U101.22 (PGND), U101.29 (EP), U102.1 (GND), U102.4 (GND), U102.6 (REF2); also elsewhere on the board
ICAP_S: C115.1, R115.2; also elsewhere on the board
ISNS_N: U101.13 (ISNS-); also elsewhere on the board
NODE: C108.1, C109.1, C110.1, C111.1, C112.1, C113.1, D101.1 (K), J101.2, Q104.5 (D), R107.1, R114.1, U101.12 (VOSNS), U101.24 (BIAS), U102.2 (+); also elsewhere on the board
unnamed: C104.2, R106.1
unnamed: J102.2, R114.2, U102.3 (-)
unnamed: Q101.3 (D), R101.2, R102.1, U101.1 (EN/UVLO)
unnamed: R115.1, U102.8
unnamed: C106.1, U101.26 (BOOT1)
unnamed: C107.1, U101.20 (BOOT2)
unnamed: C103.2, R106.2, U101.9 (COMP)
unnamed: R107.2, R108.1, U101.11 (FB)
unnamed: R109.1, U101.27 (HDRV1)
unnamed: R111.1, U101.19 (HDRV2)
unnamed: R110.1, U101.25 (LDRV1)
unnamed: R112.1, U101.21 (LDRV2)
unnamed: R104.2, U101.4 (MODE)
unnamed: R105.2, U101.6 (RT/SYNC)
unnamed: C101.2, U101.7 (SLOPE)
unnamed: C102.2, U101.8 (SS)
unnamed: C105.1, U101.23 (VCC)
PGOOD: U101.17 (PGOOD); also elsewhere on the board
VIN_C: R101.1, U101.14 (ISNS+); also elsewhere on the board
VIN_P: Q102.5 (D), U101.2 (VIN), U101.3 (VISNS); also elsewhere on the board

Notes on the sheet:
2/4 LM5176 4-switch buck-boost charger (VIN_P 22-26 V -> NODE 0-26.2 V, ~100 W)
NODE = chassis output and capacitor bank (via CM01). fsw ~248 kHz (RT 33k), Vout 26.3 V (1.5M/47k), UVLO ~19.3 V (220k/15k), CCM, hiccup off (MODE 200k: confirm in datasheet).
Power FETs: 60 V class (input TVS SMBJ30A clamps up to ~48 V). Gate nets HG1/LG1/HG2/LG2 and SW1/SW2 are local labels; keep gate loops short in layout.
CHG_INH high (default, pulled to 3V3) = converter held off. Sheet 4 pulls it low.
MODE: 200k = CCM, hiccup off (TBC)
Vout = 0.8 V x (1 + 1.5M/47k) = 26.33 V
AGND/PGND/EP: star at the EP, Kelvin CS/CSG to Rcs pads
Power stage
Valley/peak current limits: buck 80 mV, boost 120 mV typ over 12 mR -> ~6.7 A / ~10 A inductor current (L Isat 12 A). CSLOPE 220p: recheck for Rcs 12 mR.
Output node NODE (chassis + bank)
C: 4.7u 50V X7R 1206 at the boost leg. D: clamps regen spikes if the bank is cut off.
ICAP_S = 1.65 V + 40 mV/A (+ = charging bank), +-40 A range
